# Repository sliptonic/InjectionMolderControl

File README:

Injection molder digital control 
Columbia Gadget Works (2015)

This is a control system for a hobby injection molder as described in "Secrets of Building a Plastic Injection Molding Machine" by Vincent R. Gingery.

In the book, he uses a simple thermostat to control a heater element.  We wanted to try something slightly more sophisticated so we built this.

The control is housed in a small project box.  It consists of an arduino Nano on a custom board and connected to:

Two tact switches on D11 and D12 for up/down control of the temperature set point.

A Sparkfun 7-segment serial lcd display (https://www.sparkfun.com/products/11440)  The display shows a:nnn for the actual temperature and p:nnn for the setpoint.

A 10k thermister for measuring temperature of the heater block.

A Sparkfun beefcake relay control kit. (https://www.sparkfun.com/products/11042)

#########################
Status:  
#########################
It works but the interface isn't very responsive.

#########################
TODO:  
#########################

Improve the loop that detects button pushes.  
Allow push/hold for inputing the temperature.

Improve the loop that controls temperature.  PID?

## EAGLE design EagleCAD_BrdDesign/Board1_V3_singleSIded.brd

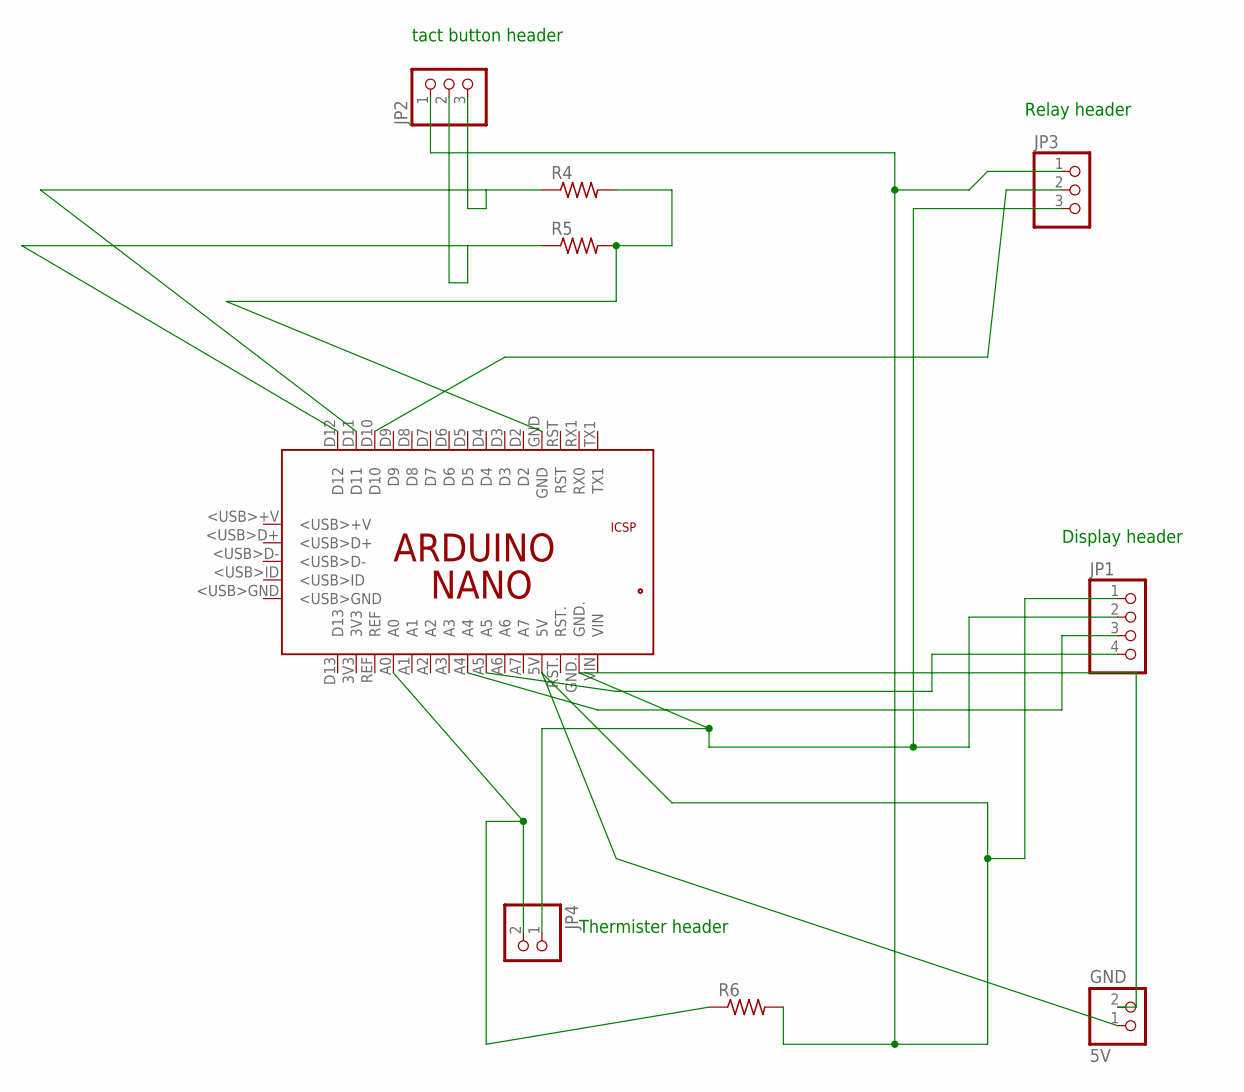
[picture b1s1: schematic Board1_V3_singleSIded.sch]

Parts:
5V: GND; 1X02/90
JP1: PINHD-1X4/90; 1X04/90
JP2, JP3: PINHD-1X3/90; 1X03/90
JP4: PINHD-1X2/90; 1X02/90
PCB1: ARDUINO_NANO
R4, R5: R-US_0207/10; 0207/10
R6: R-US_0207/15; 0207/15

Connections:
unnamed: JP2.2, PCB1.D12, R5.1
unnamed: JP4.2, PCB1.A0, R6.1
unnamed: JP3.2, PCB1.D10
unnamed: 5V.2, JP1.2, JP3.3, JP4.1, PCB1.GND.
unnamed: JP1.4, PCB1.A5
unnamed: JP1.3, PCB1.A4
unnamed: 5V.1, JP1.1, JP2.1, JP3.1, PCB1.5V, R6.2
unnamed: PCB1.GND, R4.2, R5.2
unnamed: JP2.3, PCB1.D11, R4.1

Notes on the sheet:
tact button header
Thermister header
Display header
Relay header

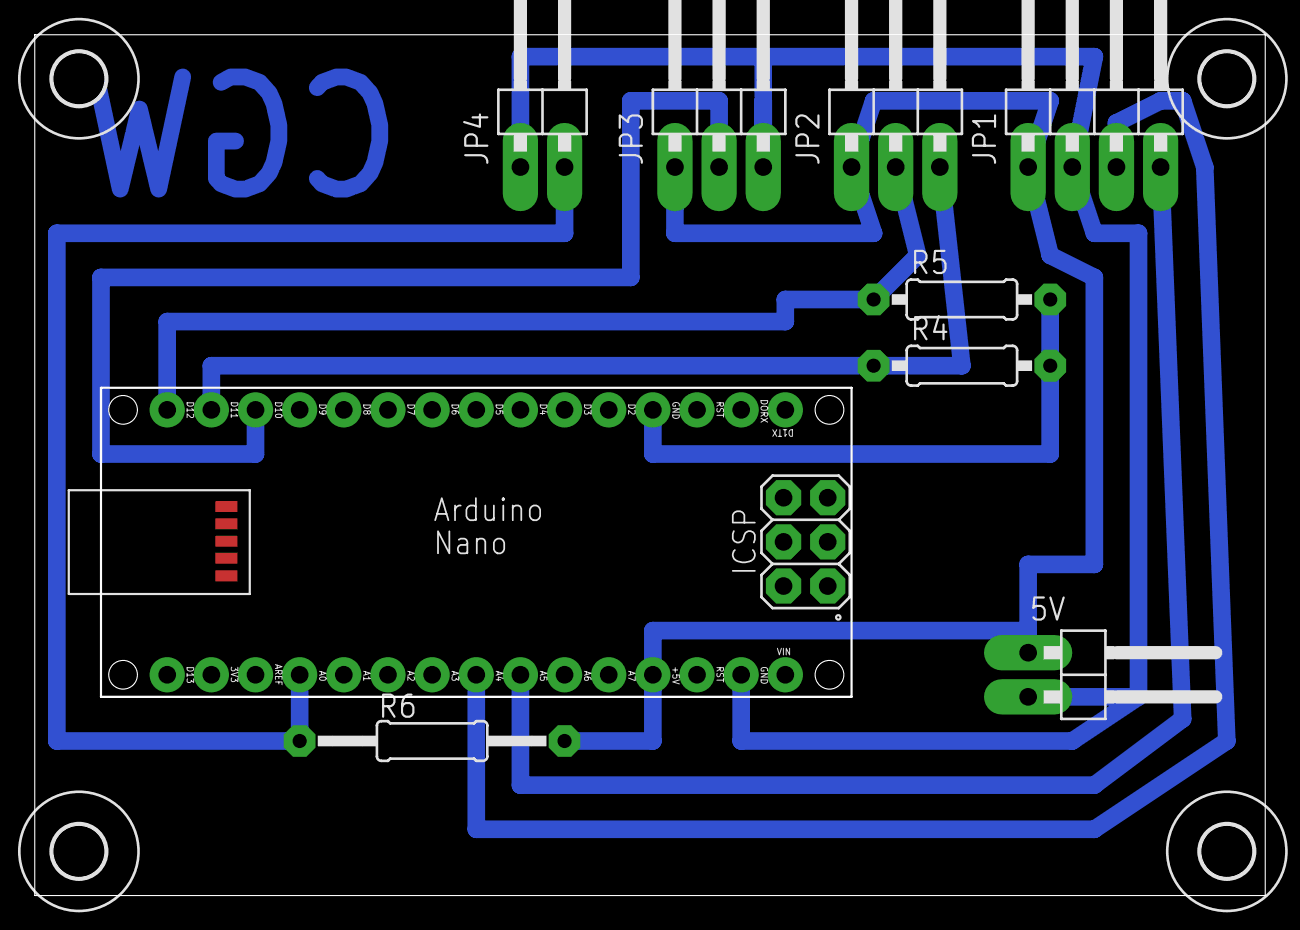
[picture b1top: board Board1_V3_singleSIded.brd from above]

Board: 2 copper layers, 70.7 x 49.4 mm, 13 parts (0 on the bottom side), 9 nets.

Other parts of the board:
U$1, U$2, U$3, U$4: 3,0

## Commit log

2015-07-17 thermistor readings reasonable now. Integrated to main project sketch file
2015-08-19 board layout
2015-08-26 eagle board design
2015-08-26 board updated
    Added resistors
2015-08-26 gcode for making board
2015-09-07 Added basic control of Beefcake relay.
    Edited README
    TODO: improve input and control loop.
